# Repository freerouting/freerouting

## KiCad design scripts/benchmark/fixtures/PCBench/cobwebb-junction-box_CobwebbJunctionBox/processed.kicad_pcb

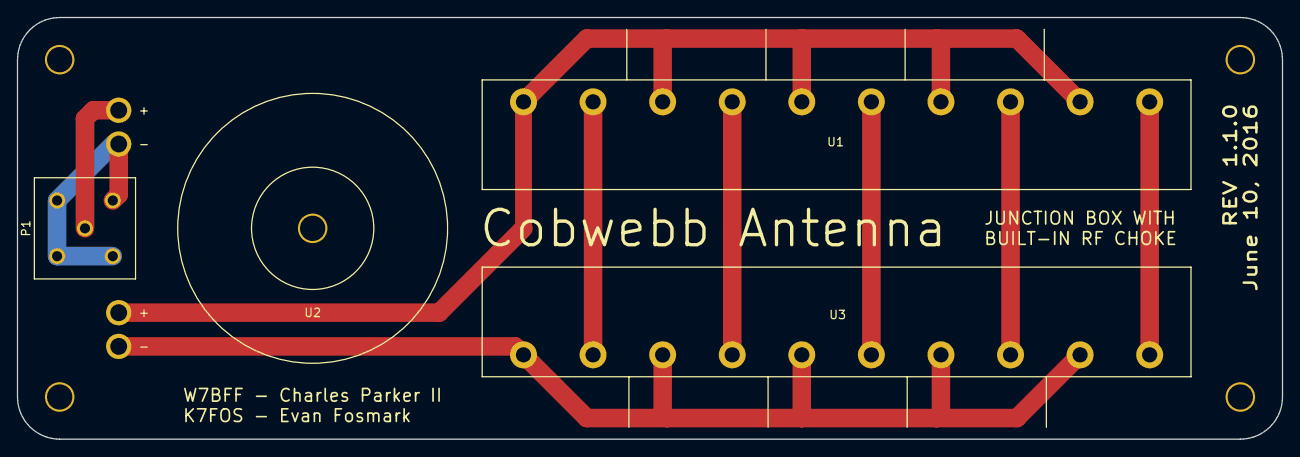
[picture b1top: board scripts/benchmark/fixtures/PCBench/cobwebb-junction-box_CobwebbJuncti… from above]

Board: 2 copper layers, 150.0 x 50.0 mm, 4 parts (0 on the bottom side), 9 nets.

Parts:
P1: BNC; BNC_Connector
U1, U3: Terminal_Block_10_Pin
U2: RF_Choke; RF_Choke_T106-2

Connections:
unnamed: P1.1, U2.2
unnamed: P1.2, U2.1
unnamed: U1.1, U3.10
unnamed: U1.3, U3.8
unnamed: U1.5, U3.6
unnamed: U1.7, U3.4
unnamed: U1.9, U3.2
unnamed: U1.2, U1.4, U1.6, U1.8, U1.10, U2.3
unnamed: U2.4, U3.1, U3.3, U3.5, U3.7, U3.9

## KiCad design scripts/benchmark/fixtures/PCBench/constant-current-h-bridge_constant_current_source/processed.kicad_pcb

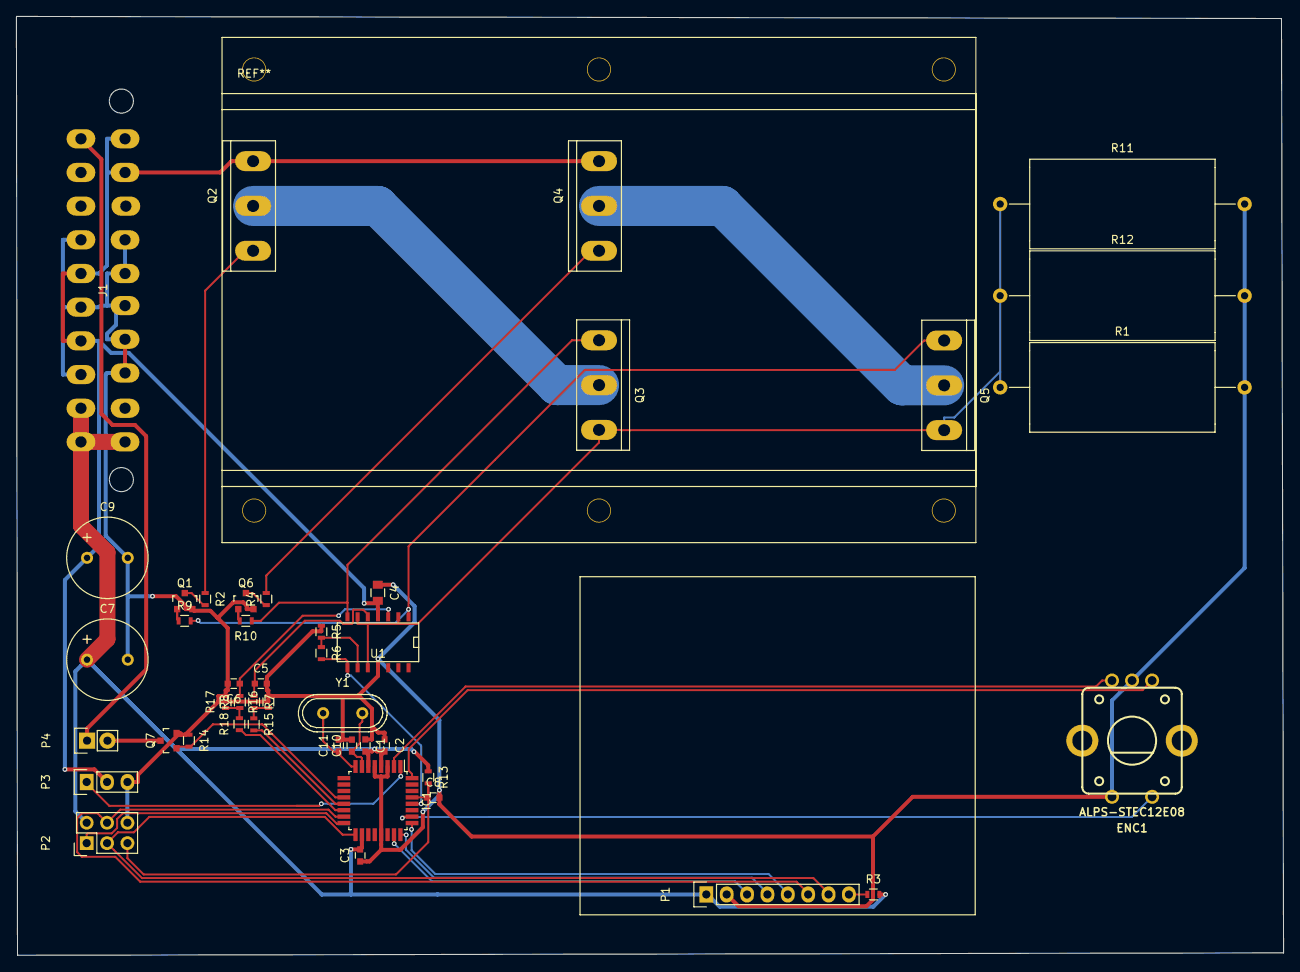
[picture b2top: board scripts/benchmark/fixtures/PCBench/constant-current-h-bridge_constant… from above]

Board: 2 copper layers, 158.0 x 117.1 mm, 45 parts (0 on the bottom side), 39 nets.

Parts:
C1, C2, C3: 100n; C_0603
C4: C; C_0805
C5, C6: 47n; C_0603
C7, C9: CP; Elko_vert_20x10mm_RM5
C8: C; C_0603
C10, C11: 22p; C_0603
ENC1: ALPS-STEC12E08
IC1: ATMEGA328P-A; TQFP-32_7x7mm_Pitch0.8mm
J1: ATX20; Molex_minifit_jr_5566_39-29-9203_20pin
P1: Nokia5110_Display
P2: CONN_02X03; Pin_Header_Straight_2x03
P3: CONN_01X03; Pin_Header_Straight_1x03
P4: CONN_01X02; Pin_Header_Straight_1x02
Q1, Q6: BC847; SOT-23
Q2, Q4: BD250; TO-247_Vertical_Neutral123
Q3, Q5: BD249; TO-247_Vertical_Neutral123
Q7: IRLML6244; SOT-23
R1, R11, R12: 0R1; Resistor_Ceramic_Horizontal_L23mm-W9mm-H9mm-p30mm
R2, R4: 1k5; R_0603
R3: 220; R_0603
R5, R9, R10, R14: 10k; R_0603
R6: 12k; R_0603
R7, R8: 100; R_0603
R13: R; R_0603
R15, R18: 180; R_0603
R16, R17: 150; R_0603
U1: LM324; SOIC-14_N
Y1: Crystal; Crystal_HC49-U_Vertical

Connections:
+3V3: C1.2, C2.2, C3.2, C7.1, IC1.4, IC1.6, IC1.18, J1.1, J1.2, J1.11, P1.1, P2.2, R3.2, R13.1
+5V: C4.2, C9.1, J1.4, J1.6, J1.19, J1.20, P3.2, Q2.3, Q4.3, U1.4
+12V: J1.10, P4.1
/MISO: IC1.16, P2.1
/MOSI: IC1.15, P1.6, P2.4
/RESET: C8.1, IC1.29, P2.5, R13.2
/SCK: IC1.17, P1.7, P2.3
/XTAL1: C10.1, IC1.7, Y1.2
/XTAL2: C11.1, IC1.8, Y1.1
/lcd_dc: IC1.25, P1.5
/lcd_rst: IC1.24, P1.4
/lcd_sce: IC1.23, P1.3
/load_1: Q2.2, Q3.2
/load_2: Q4.2, Q5.2
/mcu_adc: IC1.28, R6.2, U1.8
/mcu_airpump: IC1.12, Q7.1, R14.2
/opa_neg: Q5.1, R9.2, U1.1
/opa_pos: Q3.1, R10.1, U1.7
/pwm_neg: IC1.14, R18.1
/pwm_pos: IC1.13, R15.2
/rot_enc1: ENC1.A, IC1.32
/rot_enc2: ENC1.B, IC1.2
/rot_sw: ENC1.SW1, IC1.26
/servo_pwm: IC1.1, P3.1
GND: C1.1, C2.1, C3.1, C4.1, C5.2, C6.2, C7.2, C8.2, C9.2, C10.2, C11.2, ENC1.C, ENC1.SW2, IC1.3, IC1.5, IC1.21, J1.3, J1.5, J1.7, J1.13, J1.14, J1.15, J1.16, J1.17, P1.2, P2.6, P3.3, Q1.2, Q6.2, Q7.2, R1.2, R5.1, R11.2, R12.2, R14.1, R16.2, R17.2, U1.11
unnamed: C5.1, R7.1, U1.5
unnamed: C6.1, R8.2, U1.3
unnamed: P1.8, R3.1
unnamed: P4.2, Q7.3
unnamed: Q1.1, R9.1
unnamed: Q1.3, R2.2
unnamed: Q2.1, R2.1
unnamed: Q3.3, Q5.3, R1.1, R11.1, R12.1, U1.2, U1.6, U1.10
unnamed: Q4.1, R4.2
unnamed: Q6.1, R10.2
unnamed: Q6.3, R4.1
unnamed: R5.2, R6.1, U1.9
unnamed: R7.2, R15.1, R16.1
unnamed: R8.1, R17.1, R18.2

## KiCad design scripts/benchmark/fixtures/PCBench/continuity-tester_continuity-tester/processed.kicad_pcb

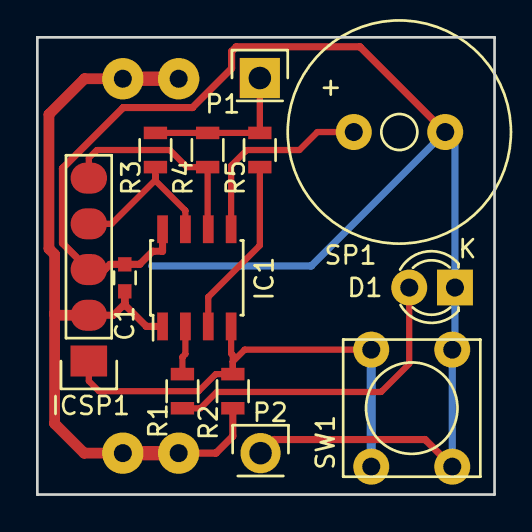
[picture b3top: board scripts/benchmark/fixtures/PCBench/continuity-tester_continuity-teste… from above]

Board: 2 copper layers, 25.4 x 25.4 mm, 14 parts (1 on the bottom side), 10 nets.

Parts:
BT1: CR2032; BAT-HLD-001-THM-OTL
C1: 100n; C_0603
D1: LED; LED-3MM
IC1: PIC12LF1571-I/SN; SOIC-8_3.9x4.9mm_Pitch1.27mm
ICSP1: CONN_01X05; Pin_Header_Straight_1x05
P1, P2: CONN_01X01; Pin_Header_Straight_1x01
R1: 4K7; R_0805
R2, R3, R4: 22k; R_0805
R5: 4k7; R_0805
SP1: SPEAKER; Buzzer_12x9.5RM7.6
SW1: SW_PUSH; SW_PUSH_SMALL

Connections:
unnamed: BT1.1, C1.1, IC1.1, ICSP1.2, R2.2
unnamed: BT1.2, C1.2, D1.1, IC1.8, ICSP1.3, P2.1, SP1.2, SW1.1
unnamed: D1.2, R1.1
unnamed: IC1.2, R1.2
unnamed: IC1.3, R5.2
unnamed: IC1.4, ICSP1.1, R2.1, SW1.2
unnamed: IC1.5, SP1.1
unnamed: IC1.6, ICSP1.5, R4.2
unnamed: IC1.7, ICSP1.4, R3.2
unnamed: P1.1, R3.1, R4.1, R5.1

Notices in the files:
scripts/benchmark/fixtures/PCBench/continuity-tester_continuity-tester/processed.kicad_pcb:
©2015
